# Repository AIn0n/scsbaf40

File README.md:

# SCSBAF40

Staggered Columns Split Budget AF 40% ergonomic keyboard

The SCSBAF40 keyboard is 40% Staggered Columns Split Budget AF ergonomic keyboard.
Heavly inspired by [REVIUNG34](https://github.com/gtips/reviung) and [Squiggle](https://github.com/ibnuda/Squiggle).

[typing demo](https://www.youtube.com/watch?v=xkb4R93yoao)

## Overview

Project goals:
- single arduino, simple design
- split
- staggered columns with dimensions fitting my fingers length
- easy to build with easily obtainable and cheap parts
- all software written in arduino IDE
- minimum 40 keys (that's main difference between this project and squiggle or reviung)

## Parts list

| Qnty | Parts | price (per piece) |
| --- | --- | --- |
| 1 | PCB | ~5$ |
| 1 | pro micro | ~3$ |
| 2 | Ethernet connector | ~1$ |
| 8 | rubber feet | <1$ |
| 40 | 1N4148 DO-35 diode | <1$ |
| 40 | MX compatible keycap (1U) | <1$ |
| 40 | MX compatible switch | 0.2$ (gateron) |

## Default layout

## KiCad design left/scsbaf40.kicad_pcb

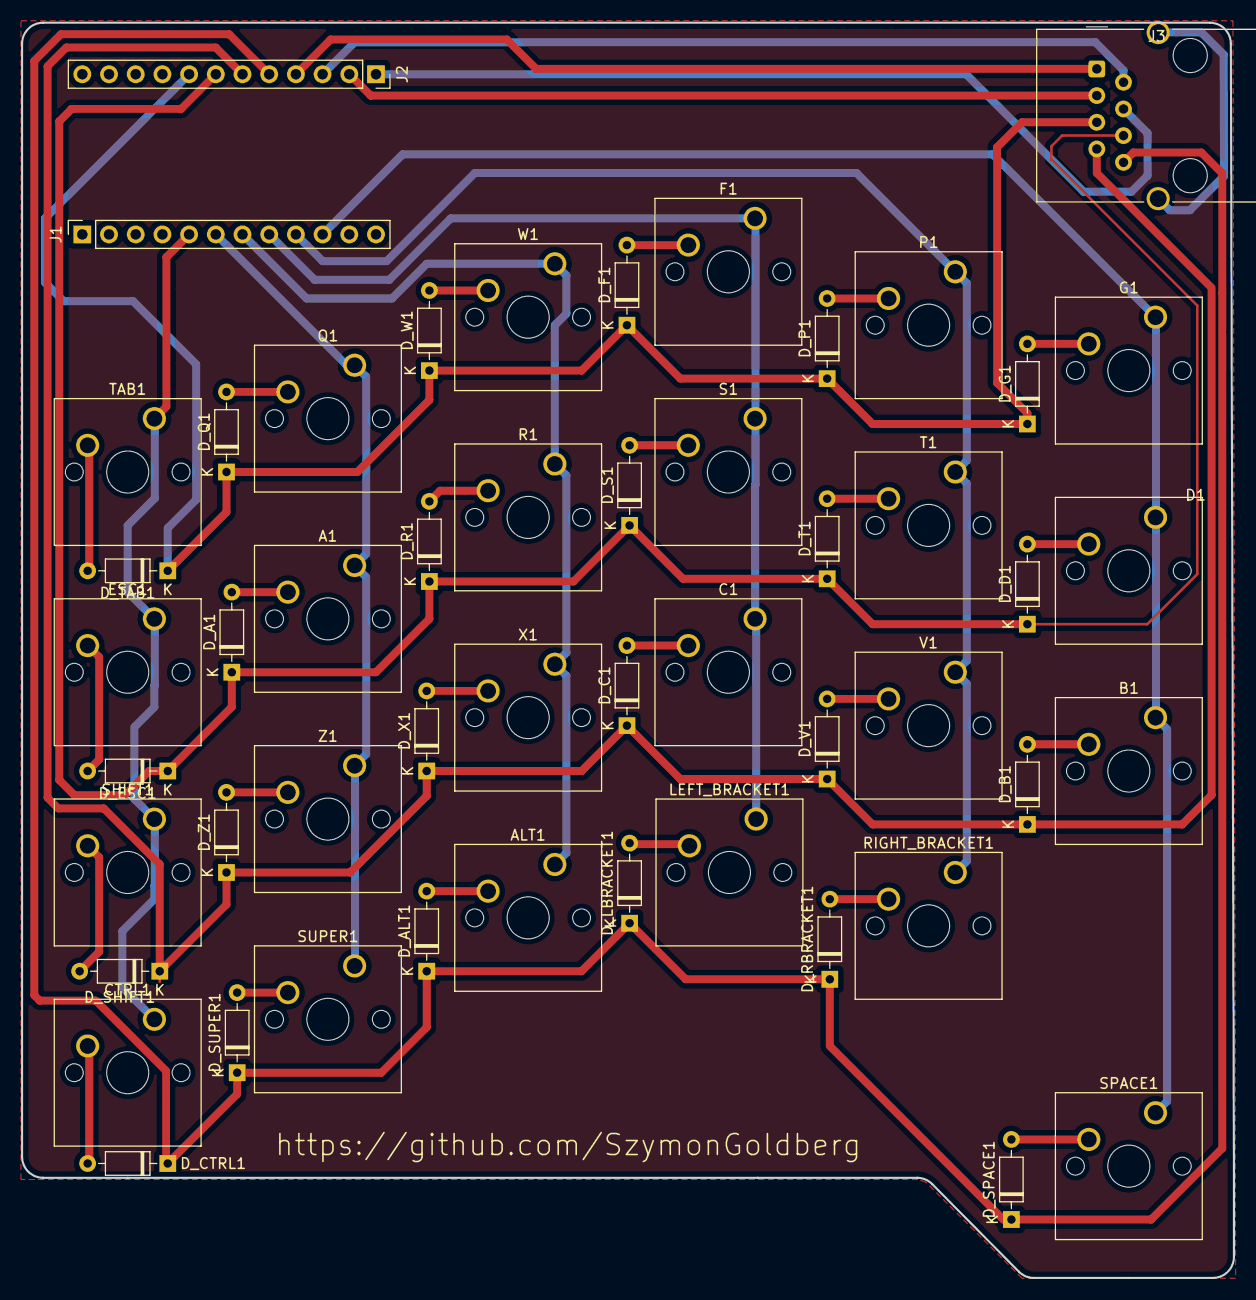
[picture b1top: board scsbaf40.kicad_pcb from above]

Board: 2 copper layers, 115.3 x 119.4 mm, 51 parts (0 on the bottom side), 38 nets.

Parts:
A1: KEYSW; SW_Cherry_MX_1.00u_PCB
ALT1: KEYSW; SW_Cherry_MX_1.00u_PCB
B1: KEYSW; SW_Cherry_MX_1.00u_PCB
C1: KEYSW; SW_Cherry_MX_1.00u_PCB
CTRL1: KEYSW; SW_Cherry_MX_1.00u_PCB
D1: KEYSW; SW_Cherry_MX_1.00u_PCB
D_A1: D; D_DO-35_SOD27_P7.62mm_Horizontal
D_ALT1: D; D_DO-35_SOD27_P7.62mm_Horizontal
D_B1: D; D_DO-35_SOD27_P7.62mm_Horizontal
D_C1: D; D_DO-35_SOD27_P7.62mm_Horizontal
D_CTRL1: D; D_DO-35_SOD27_P7.62mm_Horizontal
D_D1: D; D_DO-35_SOD27_P7.62mm_Horizontal
D_ESC1: D; D_DO-35_SOD27_P7.62mm_Horizontal
D_F1: D; D_DO-35_SOD27_P7.62mm_Horizontal
D_G1: D; D_DO-35_SOD27_P7.62mm_Horizontal
D_LBRACKET1: D; D_DO-35_SOD27_P7.62mm_Horizontal
D_P1: D; D_DO-35_SOD27_P7.62mm_Horizontal
D_Q1: D; D_DO-35_SOD27_P7.62mm_Horizontal
D_R1: D; D_DO-35_SOD27_P7.62mm_Horizontal
D_RBRACKET1: D; D_DO-35_SOD27_P7.62mm_Horizontal
D_S1: D; D_DO-35_SOD27_P7.62mm_Horizontal
D_SHIFT1: D; D_DO-35_SOD27_P7.62mm_Horizontal
D_SPACE1: D; D_DO-35_SOD27_P7.62mm_Horizontal
D_SUPER1: D; D_DO-35_SOD27_P7.62mm_Horizontal
D_T1: D; D_DO-35_SOD27_P7.62mm_Horizontal
D_TAB1: D; D_DO-35_SOD27_P7.62mm_Horizontal
D_V1: D; D_DO-35_SOD27_P7.62mm_Horizontal
D_W1: D; D_DO-35_SOD27_P7.62mm_Horizontal
D_X1: D; D_DO-35_SOD27_P7.62mm_Horizontal
D_Z1: D; D_DO-35_SOD27_P7.62mm_Horizontal
ESC1: KEYSW; SW_Cherry_MX_1.00u_PCB
F1: KEYSW; SW_Cherry_MX_1.00u_PCB
G1: KEYSW; SW_Cherry_MX_1.00u_PCB
J1, J2: Conn_01x12_Female; PinSocket_1x12_P2.54mm_Vertical
J3: 8P8C_LED_Shielded; RJ45_Wuerth_7499010001A_Horizontal
LEFT_BRACKET1: KEYSW; SW_Cherry_MX_1.00u_PCB
P1: KEYSW; SW_Cherry_MX_1.00u_PCB
Q1: KEYSW; SW_Cherry_MX_1.00u_PCB
R1: KEYSW; SW_Cherry_MX_1.00u_PCB
RIGHT_BRACKET1: KEYSW; SW_Cherry_MX_1.00u_PCB
S1: KEYSW; SW_Cherry_MX_1.00u_PCB
SHIFT1: KEYSW; SW_Cherry_MX_1.00u_PCB
SPACE1: KEYSW; SW_Cherry_MX_1.00u_PCB
SUPER1: KEYSW; SW_Cherry_MX_1.00u_PCB
T1: KEYSW; SW_Cherry_MX_1.00u_PCB
TAB1: KEYSW; SW_Cherry_MX_1.00u_PCB
V1: KEYSW; SW_Cherry_MX_1.00u_PCB
W1: KEYSW; SW_Cherry_MX_1.00u_PCB
X1: KEYSW; SW_Cherry_MX_1.00u_PCB
Z1: KEYSW; SW_Cherry_MX_1.00u_PCB

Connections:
unnamed: A1.1, J1.6, Q1.1, SUPER1.1, Z1.1
unnamed: A1.2, D_A1.2
unnamed: ALT1.1, J1.7, R1.1, W1.1, X1.1
unnamed: ALT1.2, D_ALT1.2
unnamed: B1.1, D1.1, G1.1, J1.10, SPACE1.1
unnamed: B1.2, D_B1.2
unnamed: C1.1, F1.1, J1.8, LEFT_BRACKET1.1, S1.1
unnamed: C1.2, D_C1.2
unnamed: CTRL1.1, ESC1.1, J1.5, SHIFT1.1, TAB1.1
unnamed: CTRL1.2, D_CTRL1.2
unnamed: D1.2, D_D1.2
unnamed: D_A1.1, D_D1.1, D_ESC1.1, D_R1.1, D_S1.1, D_T1.1, J2.7, J3.6
unnamed: D_ALT1.1, D_CTRL1.1, D_LBRACKET1.1, D_RBRACKET1.1, D_SPACE1.1, D_SUPER1.1, J2.5, J3.8
unnamed: D_B1.1, D_C1.1, D_SHIFT1.1, D_V1.1, D_X1.1, D_Z1.1, J2.6, J3.7
unnamed: D_ESC1.2, ESC1.2
unnamed: D_F1.1, D_G1.1, D_P1.1, D_Q1.1, D_TAB1.1, D_W1.1, J2.8, J3.5
unnamed: D_F1.2, F1.2
unnamed: D_G1.2, G1.2
unnamed: D_LBRACKET1.2, LEFT_BRACKET1.2
unnamed: D_P1.2, P1.2
unnamed: D_Q1.2, Q1.2
unnamed: D_R1.2, R1.2
unnamed: D_RBRACKET1.2, RIGHT_BRACKET1.2
unnamed: D_S1.2, S1.2
unnamed: D_SHIFT1.2, SHIFT1.2
unnamed: D_SPACE1.2, SPACE1.2
unnamed: D_SUPER1.2, SUPER1.2
unnamed: D_T1.2, T1.2
unnamed: D_TAB1.2, TAB1.2
unnamed: D_V1.2, V1.2
unnamed: D_W1.2, W1.2
unnamed: D_X1.2, X1.2
unnamed: D_Z1.2, Z1.2
unnamed: J1.9, P1.1, RIGHT_BRACKET1.1, T1.1, V1.1
unnamed: J2.1, J3.4
unnamed: J2.2, J3.3
unnamed: J2.3, J3.2
unnamed: J2.4, J3.1

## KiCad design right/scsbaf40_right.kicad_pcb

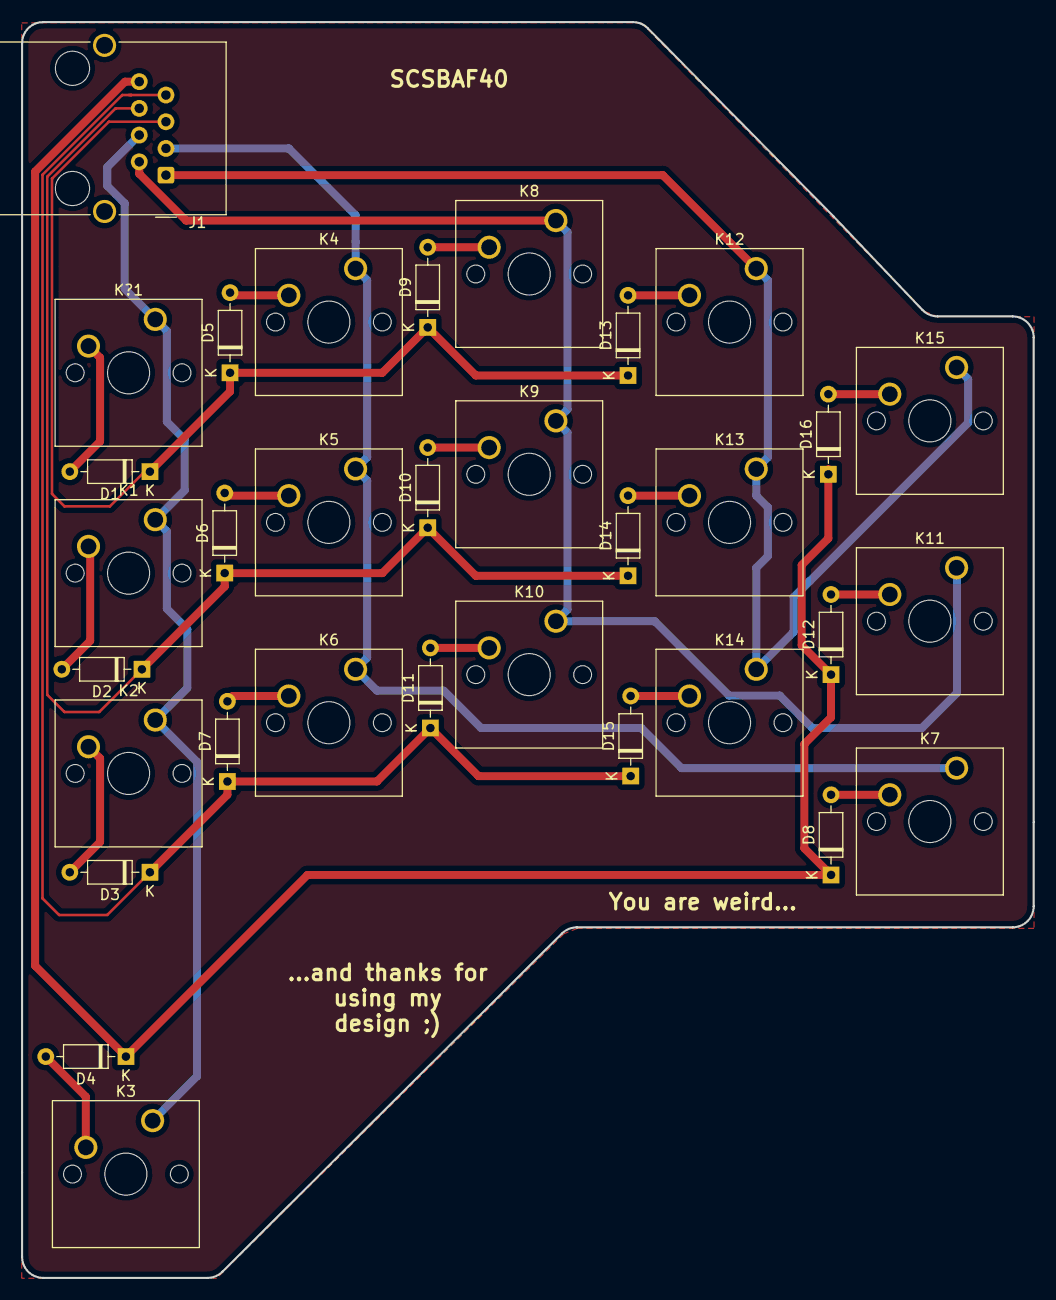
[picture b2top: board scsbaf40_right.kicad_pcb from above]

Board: 2 copper layers, 96.2 x 119.4 mm, 33 parts (0 on the bottom side), 24 nets.

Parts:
D1, D2, D3, D4, D5, D6, D7, D8, D9, D10, D11, D12, D13, D14, D15, D16: D; D_DO-35_SOD27_P7.62mm_Horizontal
J1: 8P8C_LED_Shielded; RJ45_Wuerth_7499010001A_Horizontal
K1, K2, K3, K4, K5, K6, K7, K8, K9, K10, K11, K12, K13, K14, K15: KEYSW; SW_Cherry_MX_1.00u_PCB
K?1: KEYSW; SW_Cherry_MX_1.00u_PCB

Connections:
/COL_0: J1.1, K12.1, K13.1, K14.1, K15.1
/COL_1: J1.2, K8.1, K9.1, K10.1, K11.1
/COL_2: J1.3, K4.1, K5.1, K6.1, K7.1
/COL_3: J1.4, K1.1, K2.1, K3.1, K?1.1
/ROW_0: D1.1, D5.1, D9.1, D13.1, J1.5
/ROW_1: D2.1, D6.1, D10.1, D14.1, J1.6
/ROW_2: D3.1, D7.1, D11.1, D15.1, J1.7
/ROW_3: D4.1, D8.1, D12.1, D16.1, J1.8
unnamed: D1.2, K?1.2
unnamed: D2.2, K1.2
unnamed: D3.2, K2.2
unnamed: D4.2, K3.2
unnamed: D5.2, K4.2
unnamed: D6.2, K5.2
unnamed: D7.2, K6.2
unnamed: D8.2, K7.2
unnamed: D9.2, K8.2
unnamed: D10.2, K9.2
unnamed: D11.2, K10.2
unnamed: D12.2, K11.2
unnamed: D13.2, K12.2
unnamed: D14.2, K13.2
unnamed: D15.2, K14.2
unnamed: D16.2, K15.2

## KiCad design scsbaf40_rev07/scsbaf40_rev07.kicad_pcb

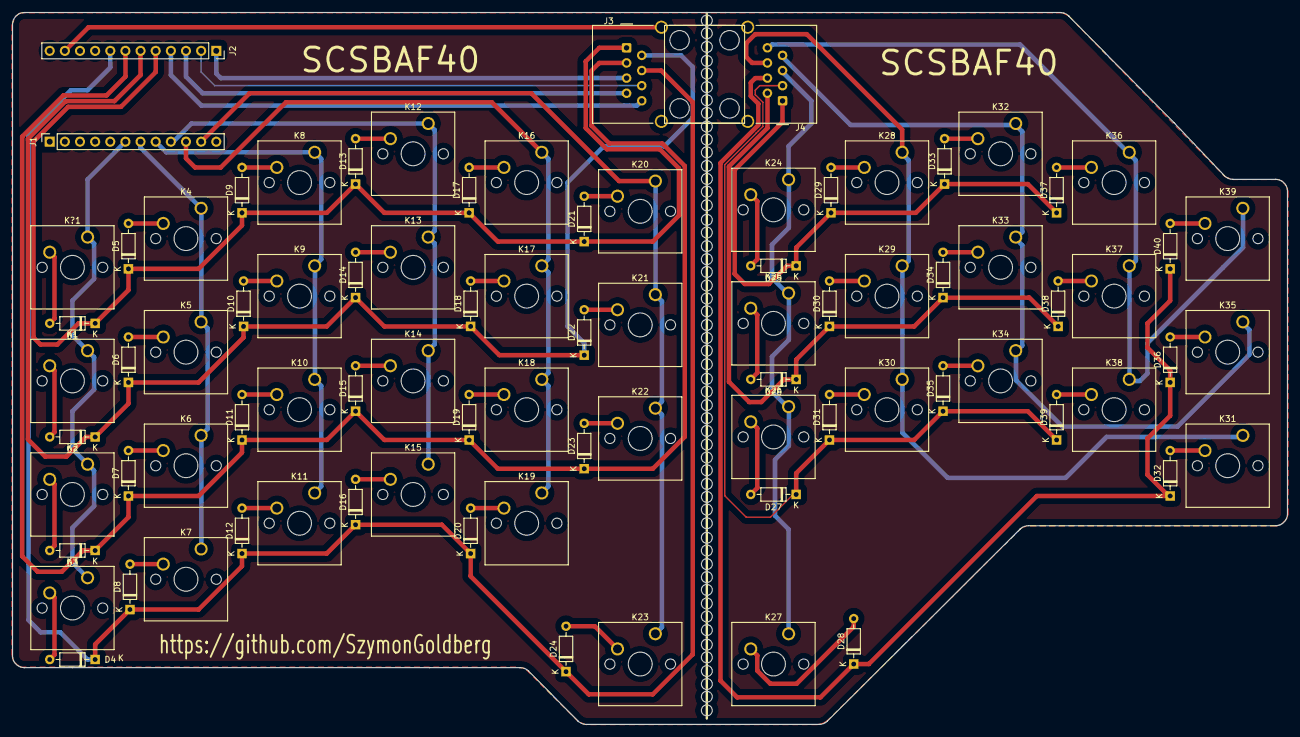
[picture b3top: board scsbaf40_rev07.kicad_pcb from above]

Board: 2 copper layers, 213.9 x 119.4 mm, 84 parts (0 on the bottom side), 63 nets.

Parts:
D1, D2, D3, D4, D5, D6, D7, D8, D9, D10, D11, D12, D13, D14, D15, D16, D17, D18, D19, D20, D21, D22, D23, D24, D25, D26, D27, D28, D29, D30, D31, D32, D33, D34, D35, D36, D37, D38, D39, D40: D; D_DO-35_SOD27_P7.62mm_Horizontal
J1, J2: Conn_01x12_Female; PinSocket_1x12_P2.54mm_Vertical
J3, J4: 8P8C_LED_Shielded; RJ45_Wuerth_7499010001A_Horizontal
K1, K2, K3, K4, K5, K6, K7, K8, K9, K10, K11, K12, K13, K14, K15, K16, K17, K18, K19, K20, K21, K22, K23, K24, K25, K26, K27, K28, K29, K30, K31, K32, K33, K34, K35, K36, K37, K38, K39: KEYSW; SW_Cherry_MX_1.00u_PCB
K?1: KEYSW; SW_Cherry_MX_1.00u_PCB

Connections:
unnamed: D1.2, K?1.2
unnamed: D2.2, K1.2
unnamed: D3.2, K2.2
unnamed: D4.2, K3.2
unnamed: D5.2, K4.2
unnamed: D6.2, K5.2
unnamed: D7.2, K6.2
unnamed: D8.2, K7.2
unnamed: D9.2, K8.2
unnamed: D10.2, K9.2
unnamed: D11.2, K10.2
unnamed: D12.2, K11.2
unnamed: D13.2, K12.2
unnamed: D14.2, K13.2
unnamed: D15.2, K14.2
unnamed: D16.2, K15.2
unnamed: D17.2, K16.2
unnamed: D18.2, K17.2
unnamed: D19.2, K18.2
unnamed: D20.2, K19.2
unnamed: D21.2, K20.2
unnamed: D22.2, K21.2
unnamed: D23.2, K22.2
unnamed: D24.2, K23.2
unnamed: D25.1, D29.1, D33.1, D37.1, J4.1
unnamed: D25.2, K24.2
unnamed: D26.1, D30.1, D34.1, D38.1, J4.2
unnamed: D26.2, K25.2
unnamed: D27.1, D31.1, D35.1, D39.1, J4.3
unnamed: D27.2, K26.2
unnamed: D28.1, D32.1, D36.1, D40.1, J4.4
unnamed: D28.2, K27.2
unnamed: D29.2, K28.2
unnamed: D30.2, K29.2
unnamed: D31.2, K30.2
unnamed: D32.2, K31.2
unnamed: D33.2, K32.2
unnamed: D34.2, K33.2
unnamed: D35.2, K34.2
unnamed: D36.2, K35.2
unnamed: D37.2, K36.2
unnamed: D38.2, K37.2
unnamed: D39.2, K38.2
unnamed: D40.2, K39.2
unnamed: J4.5, K24.1, K25.1, K26.1, K27.1
unnamed: J4.6, K28.1, K29.1, K30.1, K31.1
unnamed: J4.7, K32.1, K33.1, K34.1, K35.1
unnamed: J4.8, K36.1, K37.1, K38.1, K39.1
SHIELD: J2.11, J3.SH
col_0: J2.4, J3.8
col_1: J2.3, J3.7
col_2: J2.2, J3.6
col_3: J2.1, J3.5
col_4: J1.11, K20.1, K21.1, K22.1, K23.1
col_5: J1.10, K16.1, K17.1, K18.1, K19.1
col_6: J1.9, K12.1, K13.1, K14.1, K15.1
col_7: J1.8, K8.1, K9.1, K10.1, K11.1
col_8: J1.7, K4.1, K5.1, K6.1, K7.1
col_9: J1.6, K1.1, K2.1, K3.1, K?1.1
row_0: D1.1, D5.1, D9.1, D13.1, D17.1, D21.1, J2.5, J3.1
row_1: D2.1, D6.1, D10.1, D14.1, D18.1, D22.1, J2.6, J3.2
row_2: D3.1, D7.1, D11.1, D15.1, D19.1, D23.1, J2.7, J3.3
row_3: D4.1, D8.1, D12.1, D16.1, D20.1, D24.1, J2.8, J3.4

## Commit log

2020-10-13 Added kiCAD files.
2020-10-16 Some minor changes on PCB project
2020-11-21 Added code for pro micro
2020-11-21 Removed duplicated folder
2020-11-23 Added images
2020-11-23 Added proper readme
2020-11-23 minor readme changes
2020-11-27 Minor code cleanin
2020-11-27 Added typing demo
2020-11-27 Minor change in README
2025-02-03 minor update
2025-06-01 Added QMK files
